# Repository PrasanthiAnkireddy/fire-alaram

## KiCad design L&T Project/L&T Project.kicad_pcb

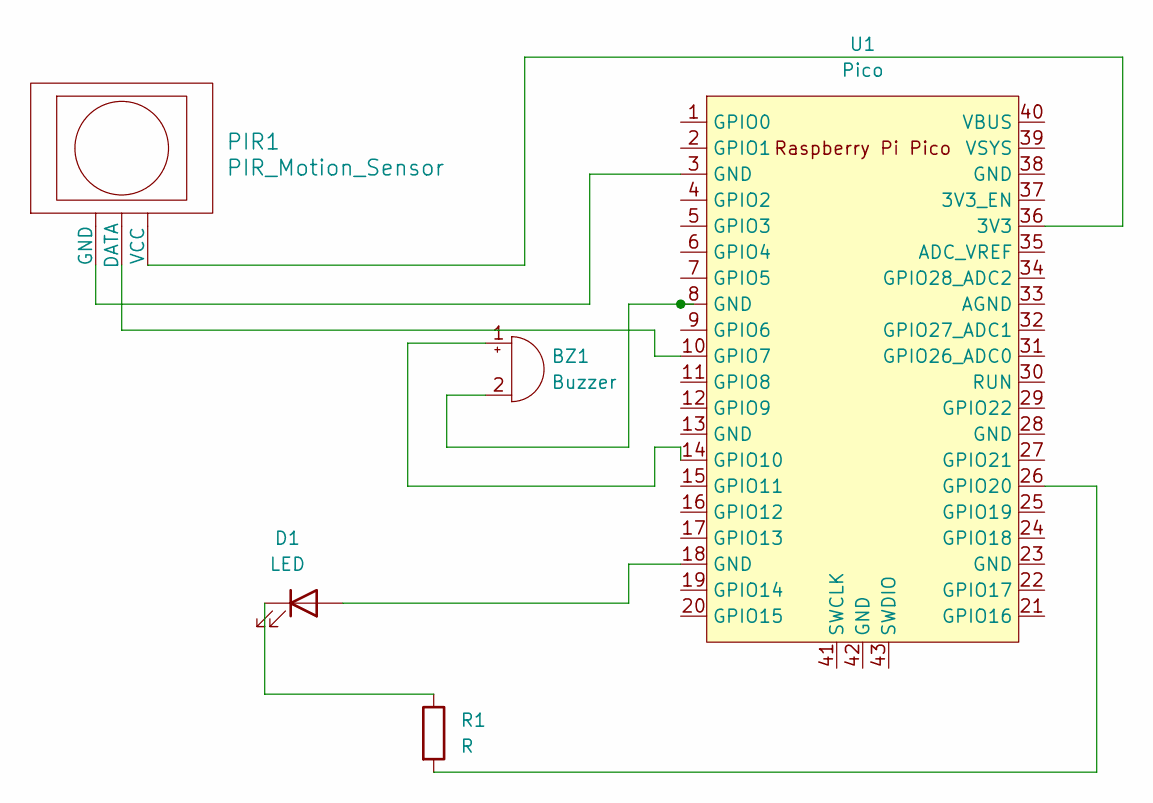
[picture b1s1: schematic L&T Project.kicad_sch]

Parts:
BZ1: Buzzer; Buzzer_D14mm_H7mm_P10mm
D1: LED; LED_Avago_PLCC4_3.2x2.8mm_CW
PIR1: PIR_Motion_Sensor
R1: R; R_0201_0603Metric
U1: Pico; RPi_Pico_SMD_TH

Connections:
unnamed: BZ1.1 (+), U1.14 (GPIO10)
unnamed: BZ1.2 (-), U1.8 (GND)
unnamed: D1.2 (A), U1.18 (GND)
unnamed: D1.1 (K), R1.1
unnamed: PIR1.2 (DATA), U1.10 (GPIO7)
unnamed: PIR1.1 (GND), U1.3 (GND)
unnamed: PIR1.3 (VCC), U1.36 (3V3)
unnamed: R1.2, U1.26 (GPIO20)

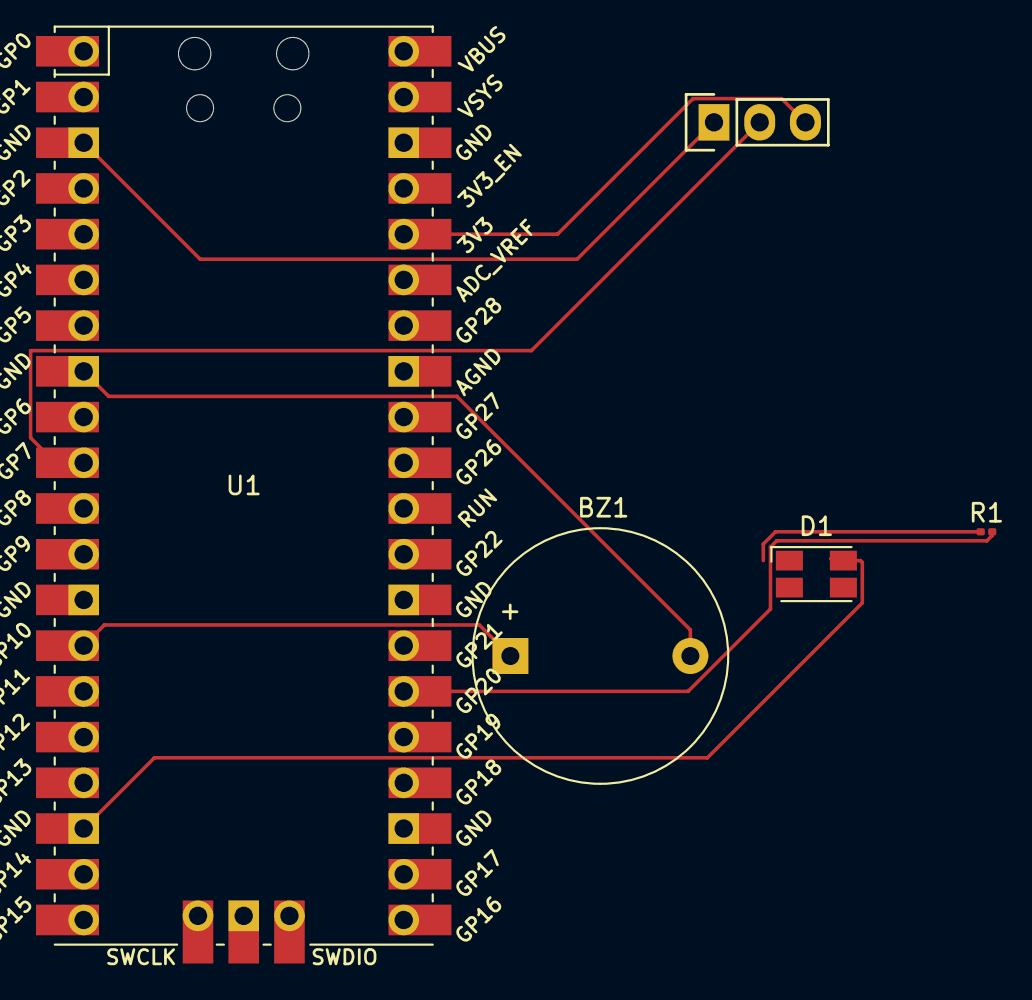
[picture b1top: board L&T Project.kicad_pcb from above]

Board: 2 copper layers, 5 parts (0 on the bottom side), 8 nets.

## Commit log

2024-04-26 Create fire_alarm
    cps project
    kicad project
2024-04-26 Fire alarm systems.py
    cps and kicad project
